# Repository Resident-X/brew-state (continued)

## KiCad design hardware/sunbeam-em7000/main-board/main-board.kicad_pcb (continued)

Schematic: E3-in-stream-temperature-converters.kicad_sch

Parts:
C640, C645: 10n; C_0603_1608Metric; Rating X7R 50V 10% 0603; MPN CL10B103KB8NNNC; LCSC C1589
C641, C642, C646, C647: 100n; C_0603_1608Metric; Rating X7R 50V 10% 0603; MPN CL10B104KB8NNNC; LCSC C1591
J620: PT1_H; JST_XH_B4B-XH-A_1x04_P2.50mm_Vertical; Rating JST XH 2.5 mm 3 A 250 V; MPN XH-4PA; LCSC C5258885
J622: PT1_2W_P; PinHeader_1x02_P2.54mm_Vertical; Rating 2.54 mm header with jumper cap; MPN 2.54-1*40P (cut) with jumper cap 2.54Sh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; LCSC C2337
J623: PT1_23W_N; PinHeader_1x02_P2.54mm_Vertical; Rating 2.54 mm header with jumper cap; MPN 2.54-1*40P (cut) with jumper cap 2.54Sh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; LCSC C2337
J625: PT2_H; JST_XH_B4B-XH-A_1x04_P2.50mm_Vertical; Rating JST XH 2.5 mm 3 A 250 V; MPN XH-4PA; LCSC C5258885
J627: PT2_2W_P; PinHeader_1x02_P2.54mm_Vertical; Rating 2.54 mm header with jumper cap; MPN 2.54-1*40P (cut) with jumper cap 2.54Sh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; LCSC C2337
J628: PT2_23W_N; PinHeader_1x02_P2.54mm_Vertical; Rating 2.54 mm header with jumper cap; MPN 2.54-1*40P (cut) with jumper cap 2.54Sh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; LCSC C2337
R640, R645: 4.02k; R_0603_1608Metric; Rating 0.1% 25ppm 0603 100mW thin film; MPN ERA3AEB4021V; LCSC C491130
R641, R646: 100k; R_0603_1608Metric; Rating 1% 100mW 75V 0603; MPN 0603WAF1003T5E; LCSC C25803
R642, R643, R647, R648: 0; R_0603_1608Metric; Rating 0603 0 ohm link; MPN 0603WAF0000T5E; LCSC C21189
R690, R691: 0; R_0603_1608Metric; Rating 0603 zero-ohm link; MPN 0603WAF0000T5E; LCSC C21189
TP620: TP_PT1_BIAS; TestPoint_Pad_D1.5mm; LCSC none
TP621: TP_PT1_RTDINP; TestPoint_Pad_D1.5mm; LCSC none
TP622: TP_PT2_BIAS; TestPoint_Pad_D1.5mm; LCSC none
TP623: TP_PT2_RTDINP; TestPoint_Pad_D1.5mm; LCSC none
TP690: TP_PT1_FORCEN_SRC; TestPoint_Pad_D1.5mm; LCSC none
TP691: TP_PT2_FORCEN_SRC; TestPoint_Pad_D1.5mm; LCSC none
U620, U621: MAX31865ATP+; TQFN-20-1EP_5x5mm_P0.65mm_EP3.1x3.1mm; Rating 4 V absolute maximum VDD and DVDD, VDD/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; MPN MAX31865ATP+T; LCSC C118474

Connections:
/In-stream temperature converters/PT1_BIAS: R640.1, TP620.1 (1_1), U620.1 (BIAS), U620.2 (REFIN+)
/In-stream temperature converters/PT1_FORCE2: R642.1, R643.1, U620.6 (FORCE2)
/In-stream temperature converters/PT1_FORCEN: J620.4, J623.2, R690.2
/In-stream temperature converters/PT1_FORCEN_SRC: R690.1, TP690.1 (1_1), U620.9 (FORCE-)
/In-stream temperature converters/PT1_FORCEP: J620.1, J622.1, R640.2, R643.2, U620.3 (REFIN-), U620.4 (ISENSOR), U620.5 (FORCE+)
/In-stream temperature converters/PT1_RTDINN: C640.2, J620.3, J623.1, U620.8 (RTDIN-)
/In-stream temperature converters/PT1_RTDINP: C640.1, J620.2, J622.2, TP621.1 (1_1), U620.7 (RTDIN+)
/In-stream temperature converters/PT2_BIAS: R645.1, TP622.1 (1_1), U621.1 (BIAS), U621.2 (REFIN+)
/In-stream temperature converters/PT2_FORCE2: R647.1, R648.1, U621.6 (FORCE2)
/In-stream temperature converters/PT2_FORCEN: J625.4, J628.2, R691.2
/In-stream temperature converters/PT2_FORCEN_SRC: R691.1, TP691.1 (1_1), U621.9 (FORCE-)
/In-stream temperature converters/PT2_FORCEP: J625.1, J627.1, R645.2, R648.2, U621.3 (REFIN-), U621.4 (ISENSOR), U621.5 (FORCE+)
/In-stream temperature converters/PT2_RTDINN: C645.2, J625.3, J628.1, U621.8 (RTDIN-)
/In-stream temperature converters/PT2_RTDINP: C645.1, J625.2, J627.2, TP623.1 (1_1), U621.7 (RTDIN+)
/PT1_CS: R641.2, U620.13 (~CS); also elsewhere on the board
/PT2_CS: R646.2, U621.13 (~CS); also elsewhere on the board
/SPI2_MISO: U620.14 (SDO), U621.14 (SDO); also elsewhere on the board
/SPI2_MOSI: U620.11 (SDI), U621.11 (SDI); also elsewhere on the board
/SPI2_SCK: U620.12 (SCLK), U621.12 (SCLK); also elsewhere on the board
GND: C641.2, C642.2, C646.2, C647.2, R642.2, R647.2, U620.10 (GND), U620.15 (DGND), U620.16 (GND), U620.21 (GND), U621.10 (GND), U621.15 (DGND), U621.16 (GND), U621.21 (GND); also elsewhere on the board

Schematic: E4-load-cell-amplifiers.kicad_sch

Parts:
C670, C672, C673, C675, C677, C678: 100n; C_0603_1608Metric; Rating X7R 50V 10% 0603; MPN CL10B104KB8NNNC; LCSC C1591
C671, C676: 10u; C_0805_2012Metric; Rating X5R 25V 10% 0805; MPN CL21A106KAYNNNE; LCSC C15850
J630: WT1_H; JST_PH_B5B-PH-K_1x05_P2.00mm_Vertical; Rating JST PH 2.0 mm 2 A 250 V; MPN KH-PH-5P-Z; LCSC C2898948
J635: WT2_H; JST_PH_B5B-PH-K_1x05_P2.00mm_Vertical; Rating JST PH 2.0 mm 2 A 250 V; MPN KH-PH-5P-Z; LCSC C2898948
R670, R671, R675, R676: 100; R_0603_1608Metric; Rating 1% 0603 100mW; MPN 0603WAF1000T5E; LCSC C22775
R672, R677: 100k; R_0603_1608Metric; Rating 1% 100mW 75V 0603; MPN 0603WAF1003T5E; LCSC C25803
TP670: TP_WT1_DATA; TestPoint_Pad_D1.0mm_Tight; LCSC none
TP671: TP_WT1_INA_P; TestPoint_Pad_D1.0mm_Tight; LCSC none
TP673: TP_WT2_INA_P; TestPoint_Pad_D1.0mm_Tight; LCSC none
U630, U631: HX711; SOIC-16_3.9x9.9mm_P1.27mm; Rating AVDD 2.6-5.5 V, DVDD 2.6-5.5 V, 24-bit,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; MPN HX711; LCSC C6705483

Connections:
/Load-cell amplifiers/WT1_INA_N: C670.2, R671.2, U630.7 (INA-)
/Load-cell amplifiers/WT1_INA_P: C670.1, R670.2, TP671.1 (1_1), U630.8 (INA+)
/Load-cell amplifiers/WT1_SN_RAW: J630.3, R671.1
/Load-cell amplifiers/WT1_SP_RAW: J630.4, R670.1
/Load-cell amplifiers/WT1_VBG: C672.1, U630.6 (VBG)
/Load-cell amplifiers/WT2_INA_N: C675.2, R676.2, U631.7 (INA-)
/Load-cell amplifiers/WT2_INA_P: C675.1, R675.2, TP673.1 (1_1), U631.8 (INA+)
/Load-cell amplifiers/WT2_SN_RAW: J635.3, R676.1
/Load-cell amplifiers/WT2_SP_RAW: J635.4, R675.1
/Load-cell amplifiers/WT2_VBG: C677.1, U631.6 (VBG)
/WT1_CLK: R672.1, U630.11 (PD_SCK); also elsewhere on the board
/WT1_DATA: TP670.1 (1_1), U630.12 (DOUT); also elsewhere on the board
/WT2_CLK: R677.1, U631.11 (PD_SCK); also elsewhere on the board
/WT2_DATA: U631.12 (DOUT); also elsewhere on the board
GND: C671.2, C672.2, C673.2, C676.2, C677.2, C678.2, J630.2, J630.5, J635.2, J635.5, R672.2, R677.2, U630.4 (VFB), U630.5 (AGND), U630.9 (INB-), U630.10 (INB+), U630.14 (XI), U630.15 (RATE), U631.4 (VFB), U631.5 (AGND), U631.9 (INB-), U631.10 (INB+), U631.14 (XI), U631.15 (RATE); also elsewhere on the board

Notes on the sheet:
Channel B, on-chip oscillator and 10 SPS rate unused

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
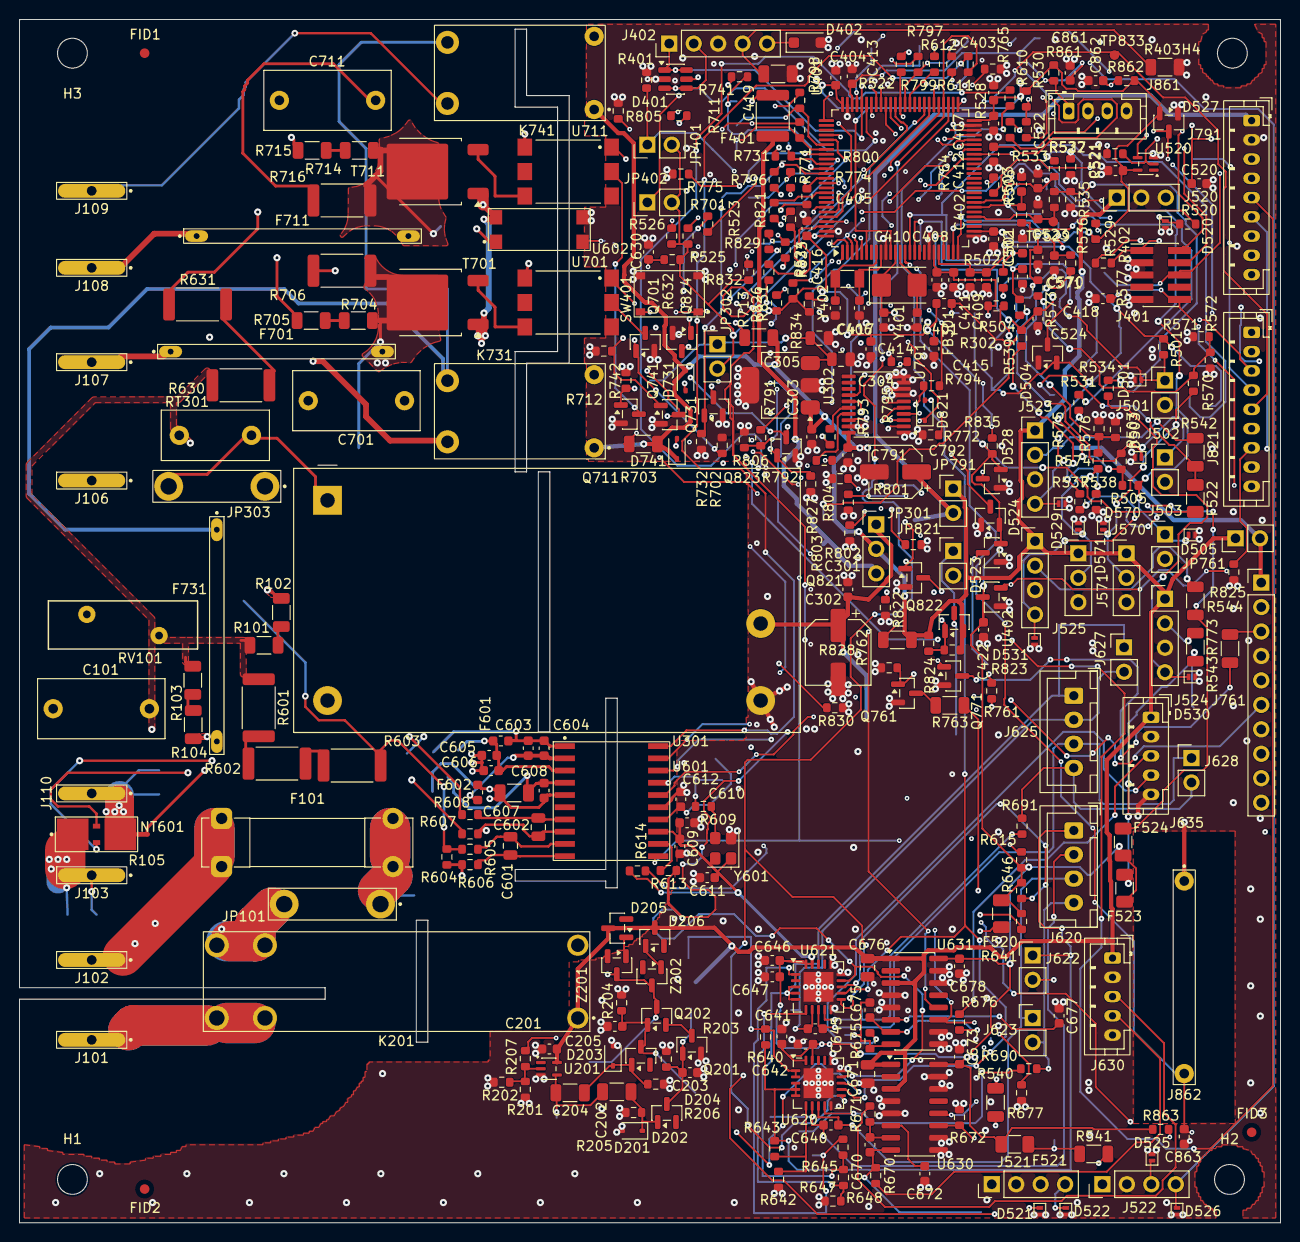
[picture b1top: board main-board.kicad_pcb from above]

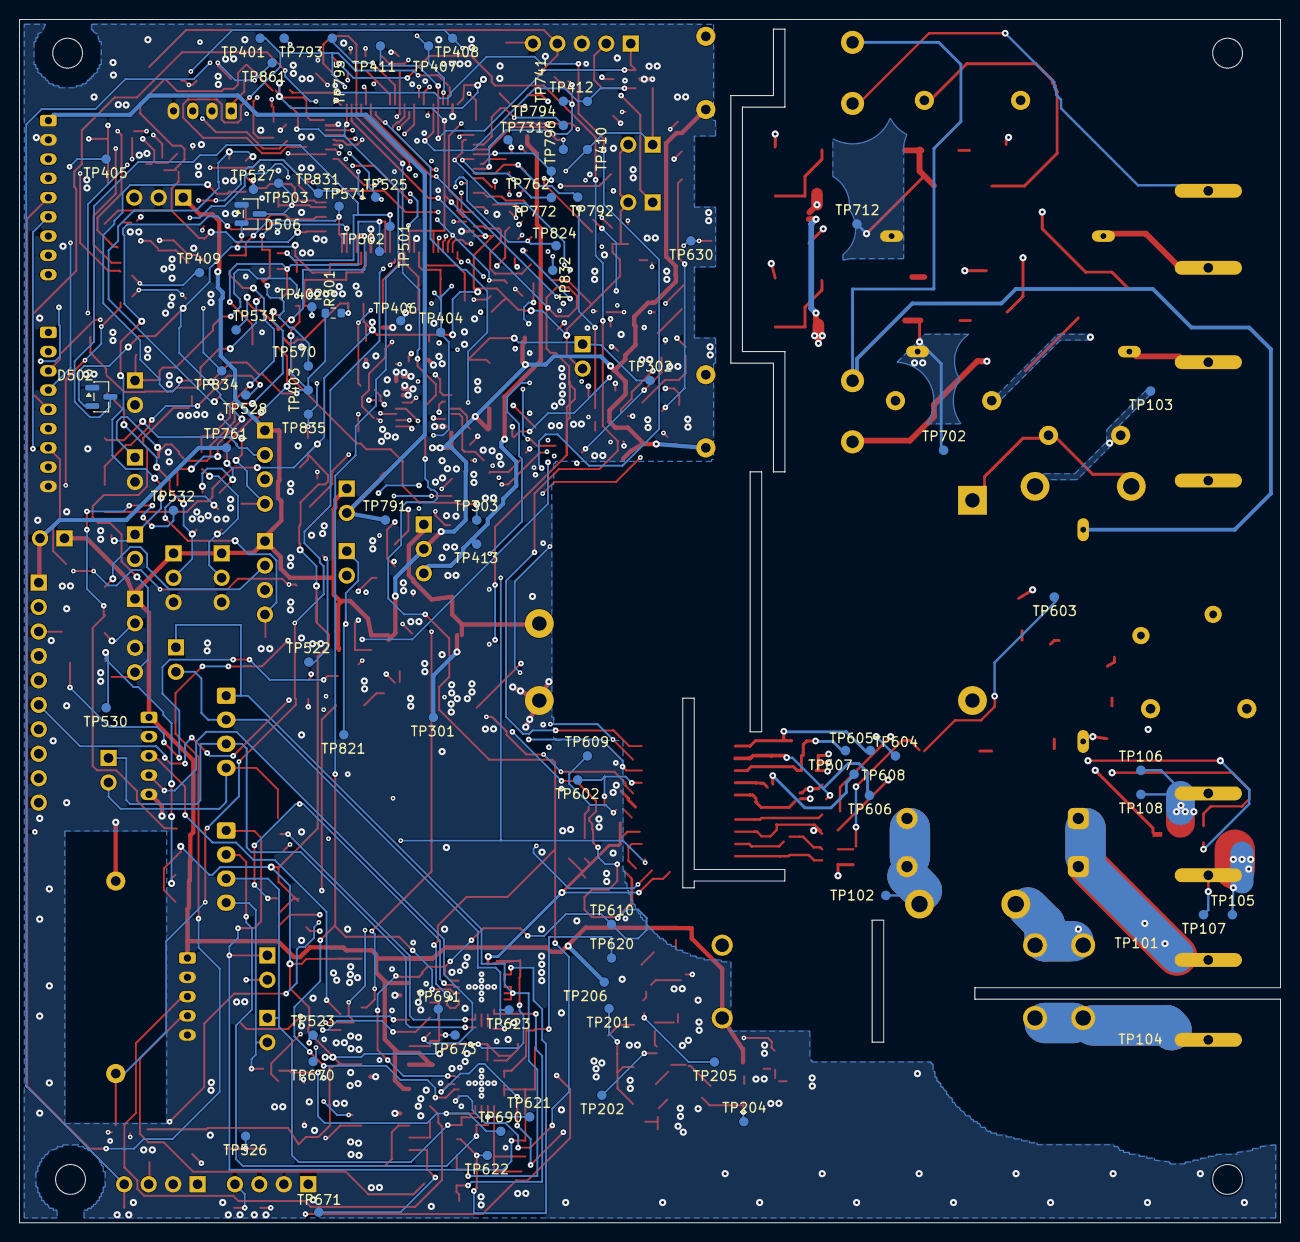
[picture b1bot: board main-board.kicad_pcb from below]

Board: 6 copper layers, 131.0 x 125.0 mm, 444 parts (85 on the bottom side), 230 nets.

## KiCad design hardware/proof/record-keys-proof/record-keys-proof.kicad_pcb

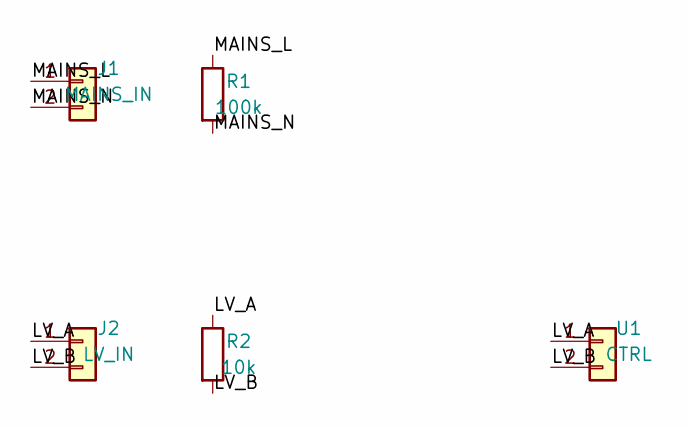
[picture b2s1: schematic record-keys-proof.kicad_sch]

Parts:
J1: MAINS_IN; PinHeader_1x02_P2.54mm_Vertical; LCSC C9000001
J2: LV_IN; PinHeader_1x02_P2.54mm_Vertical; LCSC C9000003
R1: 100k; R_Axial_DIN0207_L6.3mm_D2.5mm_P10.16mm_Horizontal; Rating 0.25W; LCSC C9000002
R2: 10k; R_Axial_DIN0207_L6.3mm_D2.5mm_P10.16mm_Horizontal; Rating 0.25W; LCSC C9000004
U1: CTRL; Controller_1x02; LCSC C9000005

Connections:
/LV_A: J2.1, R2.1, U1.1 (PA0)
/LV_B: J2.2, R2.2, U1.2 (PA1)
/MAINS_L: J1.1, R1.1
/MAINS_N: J1.2, R1.2

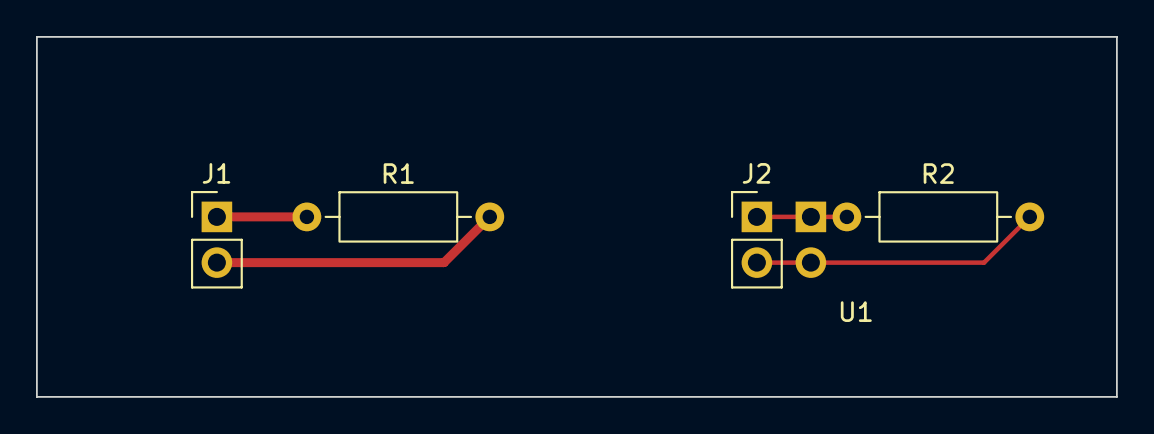
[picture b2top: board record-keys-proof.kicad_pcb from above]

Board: 2 copper layers, 60.0 x 20.0 mm, 5 parts (0 on the bottom side), 4 nets.

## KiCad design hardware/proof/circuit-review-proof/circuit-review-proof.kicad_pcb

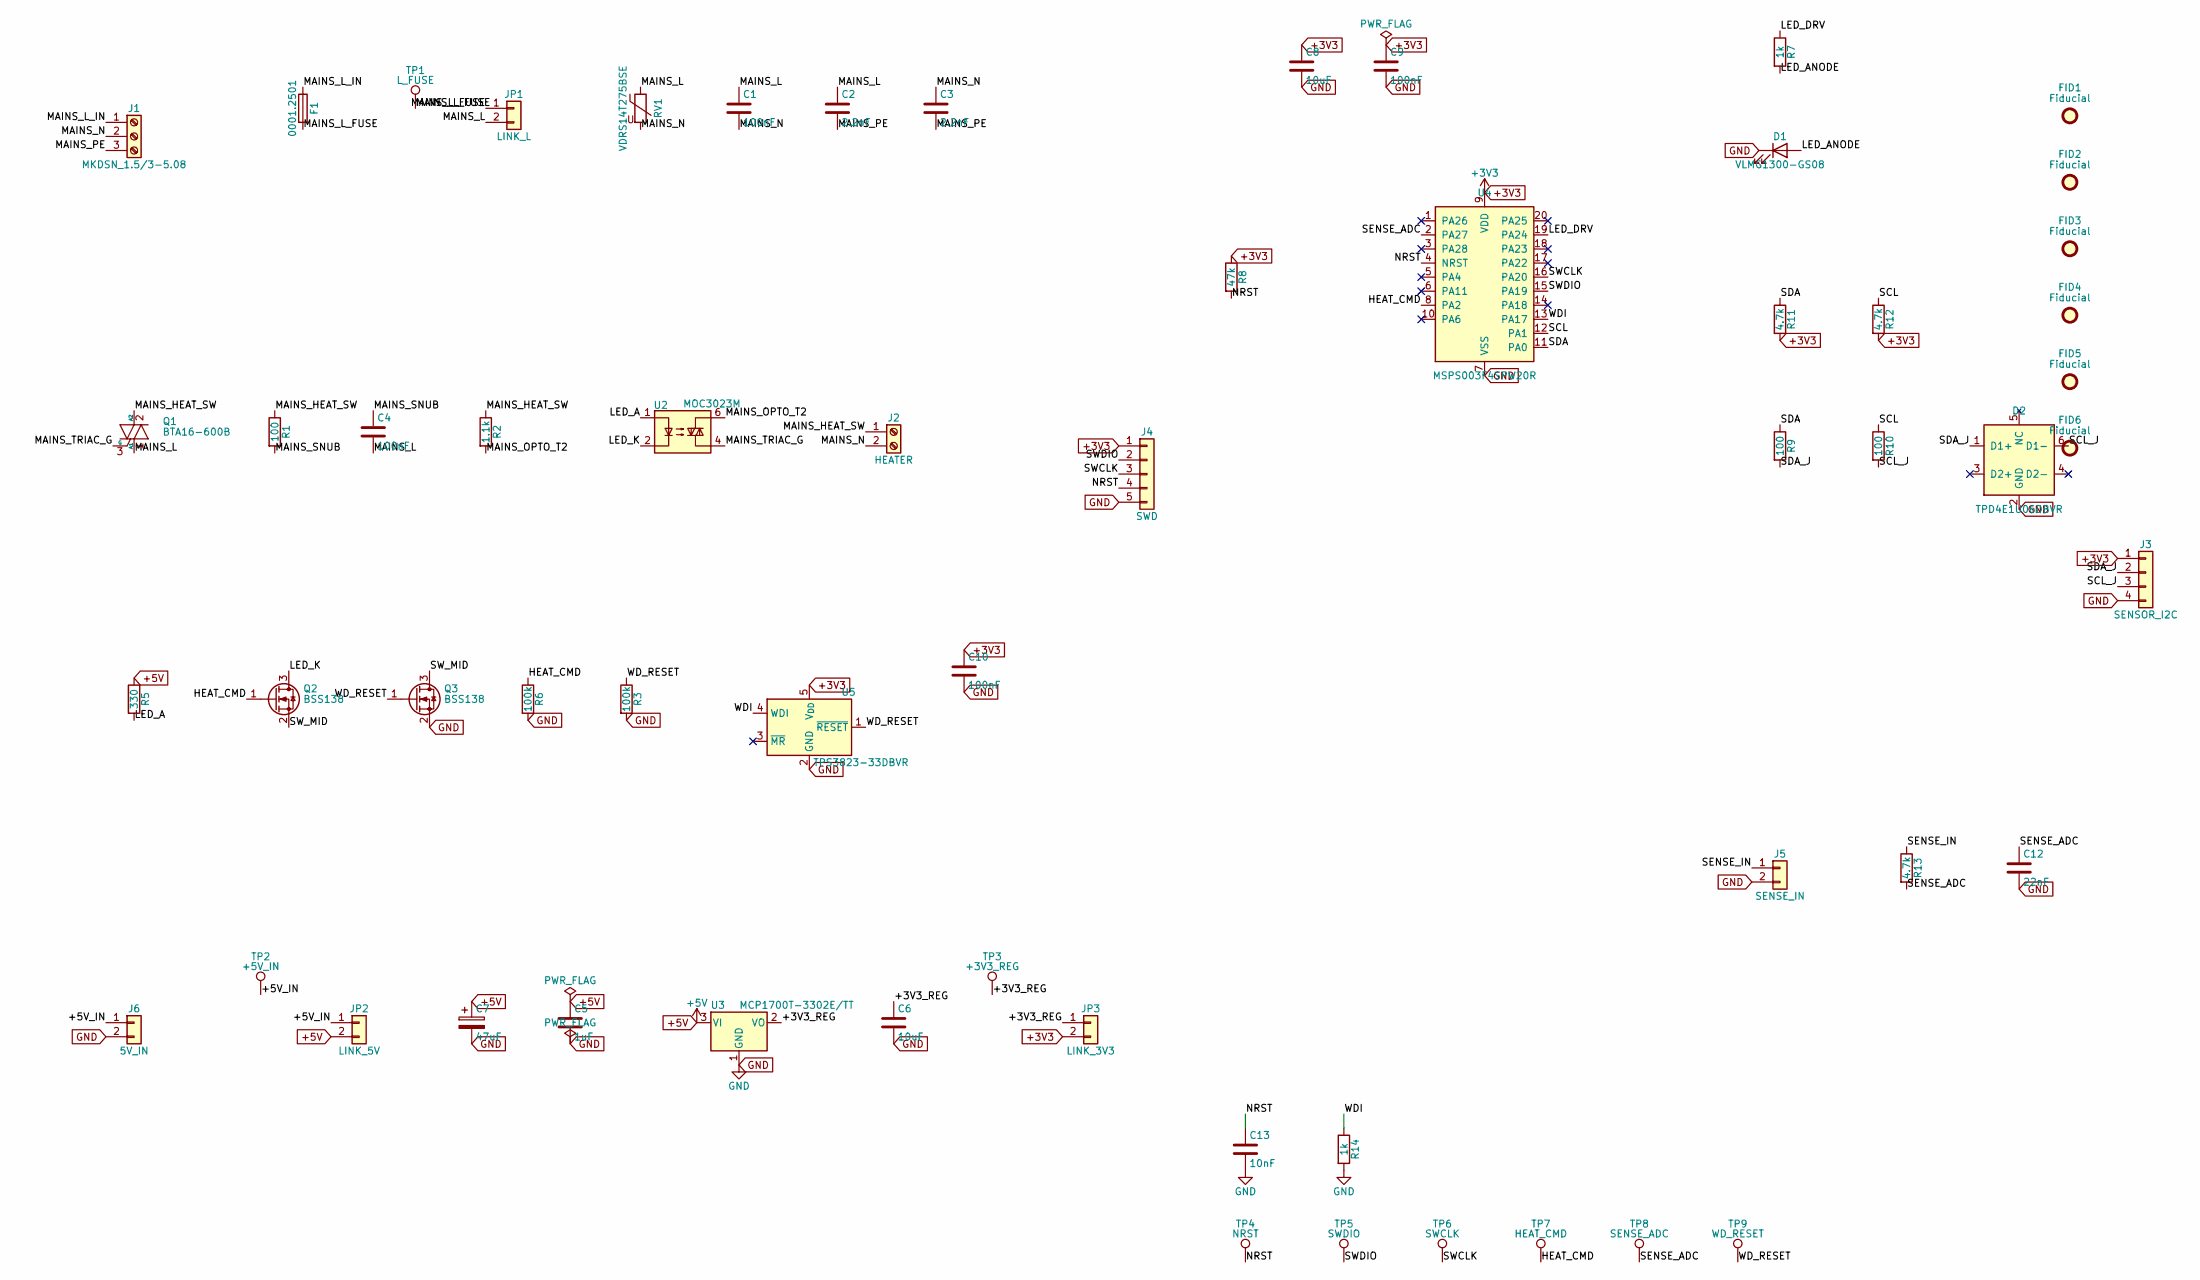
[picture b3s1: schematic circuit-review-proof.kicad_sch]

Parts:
C1, C4: 100nF; C_Rect_L18.0mm_W7.0mm_P15.00mm_FKS3_FKP3; Rating 275VAC; LCSC C9200007
C2, C3: 2.2nF; C_Disc_D7.0mm_W2.5mm_P5.00mm; Rating 250VAC; LCSC C9200008
C5: 1uF; C_0603_1608Metric; Rating 16V; LCSC C9200029
C6, C8: 10uF; C_0805_2012Metric; Rating 10V; LCSC C9200031
C7: 47uF; CP_EIA-3528-21_Kemet-B; Rating 10V; LCSC C9200028
C9, C10: 100nF; C_0603_1608Metric; Rating 16V; LCSC C9200021
C12: 22nF; C_0603_1608Metric; Rating 16V; LCSC C9200037
C13: 10nF; C_0603_1608Metric; Rating 16V; LCSC C9200036
D1: VLMG1300-GS08; LED_0603_1608Metric; Rating 30mA; LCSC C9200034
D2: TPD4E1U06DBVR; SOT-23-6; Rating 5.5V; LCSC C9200035
F1: 0001.2501; Fuseholder_Cylinder-5x20mm_Bulgin_FX0457_Horizontal_Closed; Rating 500mA 250VAC; LCSC C9200003
FID1, FID2, FID3, FID4, FID5, FID6: Fiducial; Fiducial_1mm_Mask2mm; LCSC C9200038
J1: MKDSN_1.5/3-5.08; TerminalBlock_Phoenix_MKDS-1,5-3-5.08_1x03_P5.08mm_Horizont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; Rating 320VAC 8A; LCSC C9200001
J2: HEATER; TerminalBlock_Phoenix_MKDS-1,5-2-5.08_1x02_P5.08mm_Horizont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; Rating 320VAC 8A; LCSC C9200002
J3: SENSOR_I2C; JST_XH_B4B-XH-A_1x04_P2.50mm_Vertical; Rating 3A 250V; LCSC C9200025
J4: SWD; PinHeader_1x05_P2.54mm_Vertical; Rating 3A; LCSC C9200033
J5: SENSE_IN; JST_XH_B2B-XH-A_1x02_P2.50mm_Vertical; Rating 3A 250V; LCSC C9200024
J6: 5V_IN; JST_XH_B2B-XH-A_1x02_P2.50mm_Vertical; Rating 3A 250V; LCSC C9200023
JP1: LINK_L; SolderWire-1sqmm_1x02_P7.8mm_D1.4mm_OD3.9mm; Rating 300VAC 6A; LCSC C9200005
JP2: LINK_5V; PinHeader_1x02_P2.54mm_Vertical; Rating 3A; LCSC C9200026
JP3: LINK_3V3; PinHeader_1x02_P2.54mm_Vertical; Rating 3A; LCSC C9200027
Q1: BTA16-600B; TO-220-3_Vertical; Rating 600V 16A; LCSC C9200009
Q2, Q3: BSS138; SOT-23; Rating 50V 0.22A; LCSC C9200014
R1: 100; R_2512_6332Metric; Rating 1W; LCSC C9200010
R2: 1.1k; R_1206_3216Metric; Rating 0.25W; LCSC C9200011
R3, R6: 100k; R_0603_1608Metric; Rating 0.1W; LCSC C9200015
R5: 330; R_1206_3216Metric; Rating 0.25W; LCSC C9200013
R7, R14: 1k; R_0603_1608Metric; Rating 0.1W; LCSC C9200017
R8: 47k; R_0603_1608Metric; Rating 0.1W; LCSC C9200016
R9, R10: 100; R_0603_1608Metric; Rating 0.1W; LCSC C9200018
R11, R12, R13: 4.7k; R_0603_1608Metric; Rating 0.1W; LCSC C9200019
RV1: VDRS14T275BSE; RV_Disc_D15.5mm_W5.4mm_P7.5mm; Rating 275VAC; LCSC C9200006
TP1: L_FUSE; TestPoint_Pad_D1.0mm; Rating 1A; LCSC C9200004
TP2: +5V_IN; TestPoint_Pad_D1.0mm; Rating 1A; LCSC C9200004
TP3: +3V3_REG; TestPoint_Pad_D1.0mm; Rating 1A; LCSC C9200004
TP4: NRST; TestPoint_Pad_D1.0mm; Rating 1A; LCSC C9200004
TP5: SWDIO; TestPoint_Pad_D1.0mm; Rating 1A; LCSC C9200004
TP6: SWCLK; TestPoint_Pad_D1.0mm; Rating 1A; LCSC C9200004
TP7: HEAT_CMD; TestPoint_Pad_D1.0mm; Rating 1A; LCSC C9200004
TP8: SENSE_ADC; TestPoint_Pad_D1.0mm; Rating 1A; LCSC C9200004
TP9: WD_RESET; TestPoint_Pad_D1.0mm; Rating 1A; LCSC C9200004
U2: MOC3023M; DIP-6_W7.62mm; Rating 400V; LCSC C9200012
U3: MCP1700T-3302E/TT; SOT-23; Rating 6V; LCSC C9200030
U4: MSPS003F4SPW20R; TSSOP-20_4.4x6.5mm_P0.65mm; Rating 4.1V; LCSC C9200032
U5: TPS3823-33DBVR; SOT-23-5; Rating 6V; LCSC C9200020

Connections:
/+3V3_REG: C6.1, JP3.1, TP3.1, U3.2 (VO)
/+5V_IN: J6.1, JP2.1, TP2.1
/HEAT_CMD: Q2.1 (G), R6.1, TP7.1, U4.8 (PA2)
/LED_A: R5.2, U2.1
/LED_ANODE: D1.2 (A), R7.2
/LED_DRV: R7.1, U4.19 (PA24)
/LED_K: Q2.3 (D), U2.2
/MAINS_HEAT_SW: J2.1, Q1.2 (A2), R1.1, R2.1
/MAINS_L: C1.1, C2.1, C4.2, JP1.2, Q1.1 (A1), RV1.1
/MAINS_L_FUSE: F1.2, JP1.1, TP1.1
/MAINS_L_IN: F1.1, J1.1
/MAINS_N: C1.2, C3.1, J1.2, J2.2, RV1.2
/MAINS_OPTO_T2: R2.2, U2.6
/MAINS_PE: C2.2, C3.2, J1.3
/MAINS_SNUB: C4.1, R1.2
/MAINS_TRIAC_G: Q1.3 (G), U2.4
/NRST: C13.1, J4.4, R8.2, TP4.1, U4.4 (NRST)
/SCL: R10.1, R12.1, U4.12 (PA1)
/SCL_J: D2.6 (D1-), J3.3, R10.2
/SDA: R9.1, R11.1, U4.11 (PA0)
/SDA_J: D2.1 (D1+), J3.2, R9.2
/SENSE_ADC: C12.1, R13.2, TP8.1, U4.2 (PA27)
/SENSE_IN: J5.1, R13.1
/SWCLK: J4.3, TP6.1, U4.16 (PA20)
/SWDIO: J4.2, TP5.1, U4.15 (PA19)
/SW_MID: Q2.2 (S), Q3.3 (D)
/WDI: R14.1, U4.13 (PA17), U5.4 (WDI)
/WD_RESET: Q3.1 (G), R3.1, TP9.1, U5.1 (~RESET)

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
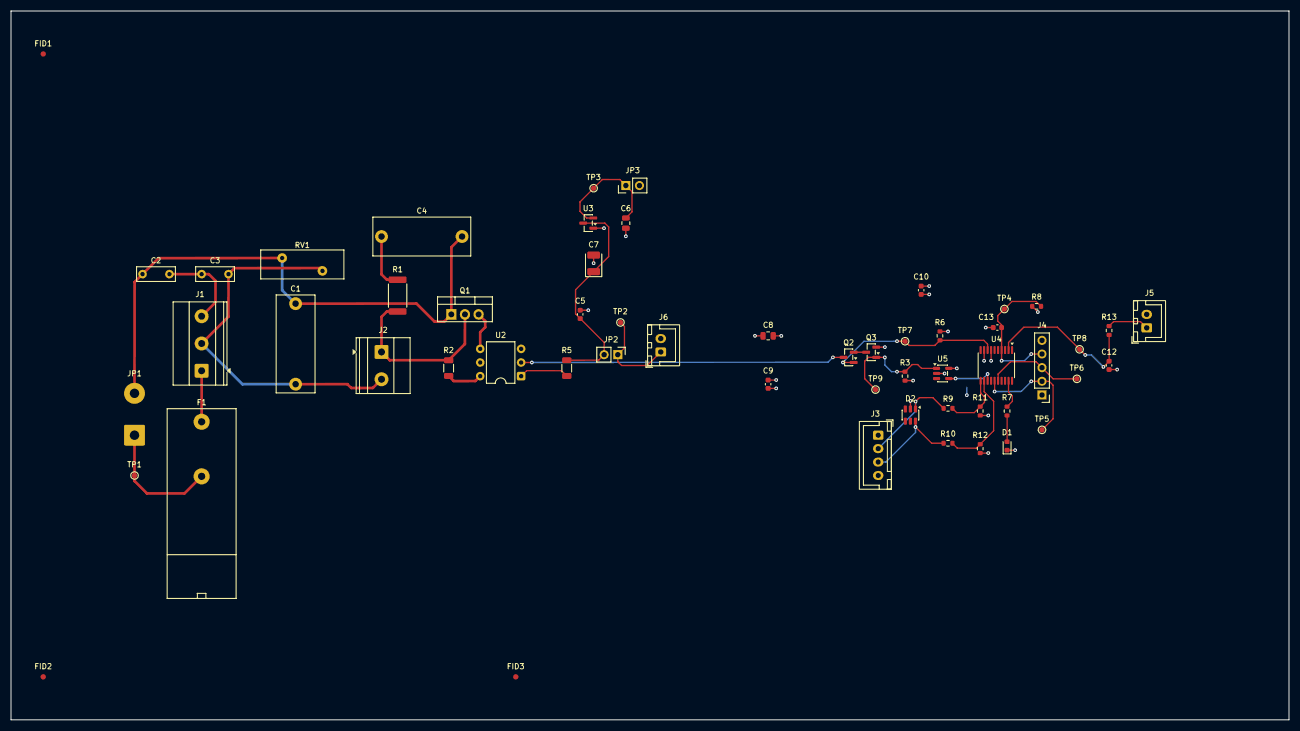
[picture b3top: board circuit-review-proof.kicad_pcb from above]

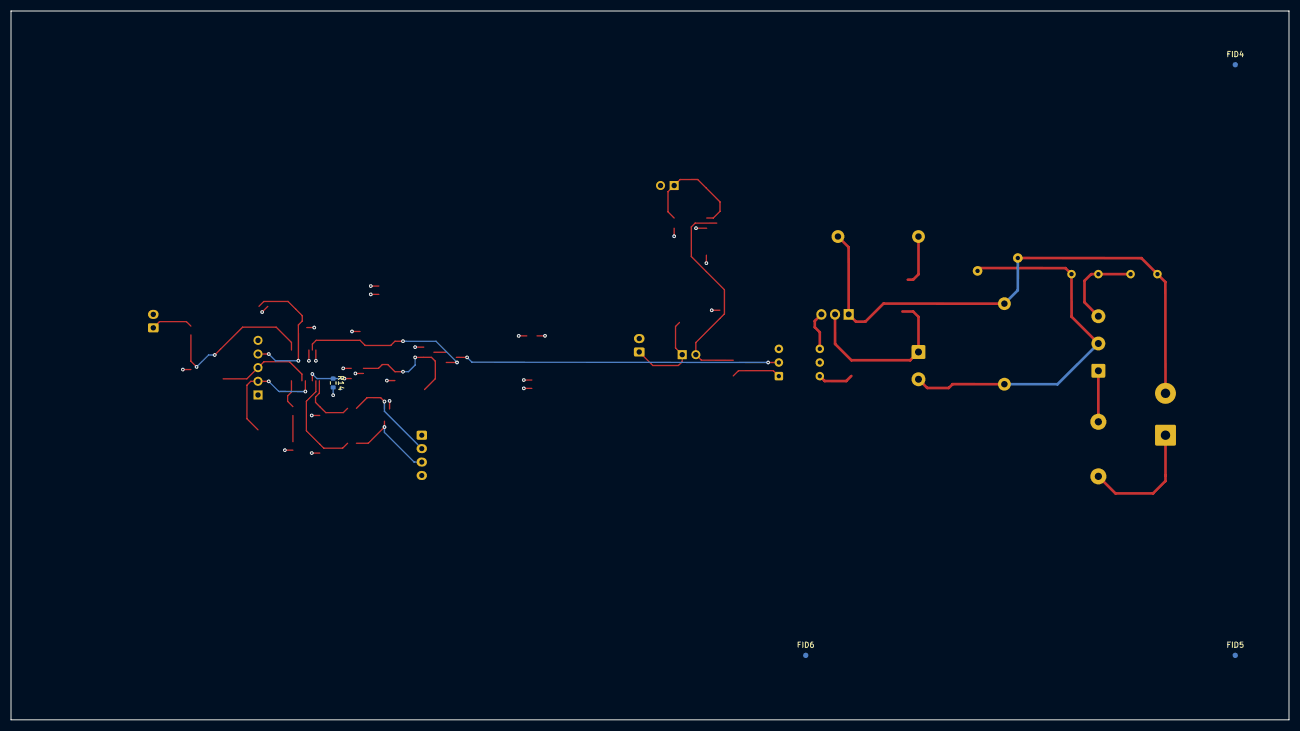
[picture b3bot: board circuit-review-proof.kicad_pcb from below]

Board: 4 copper layers, 238.0 x 132.0 mm, 60 parts (4 on the bottom side), 31 nets.

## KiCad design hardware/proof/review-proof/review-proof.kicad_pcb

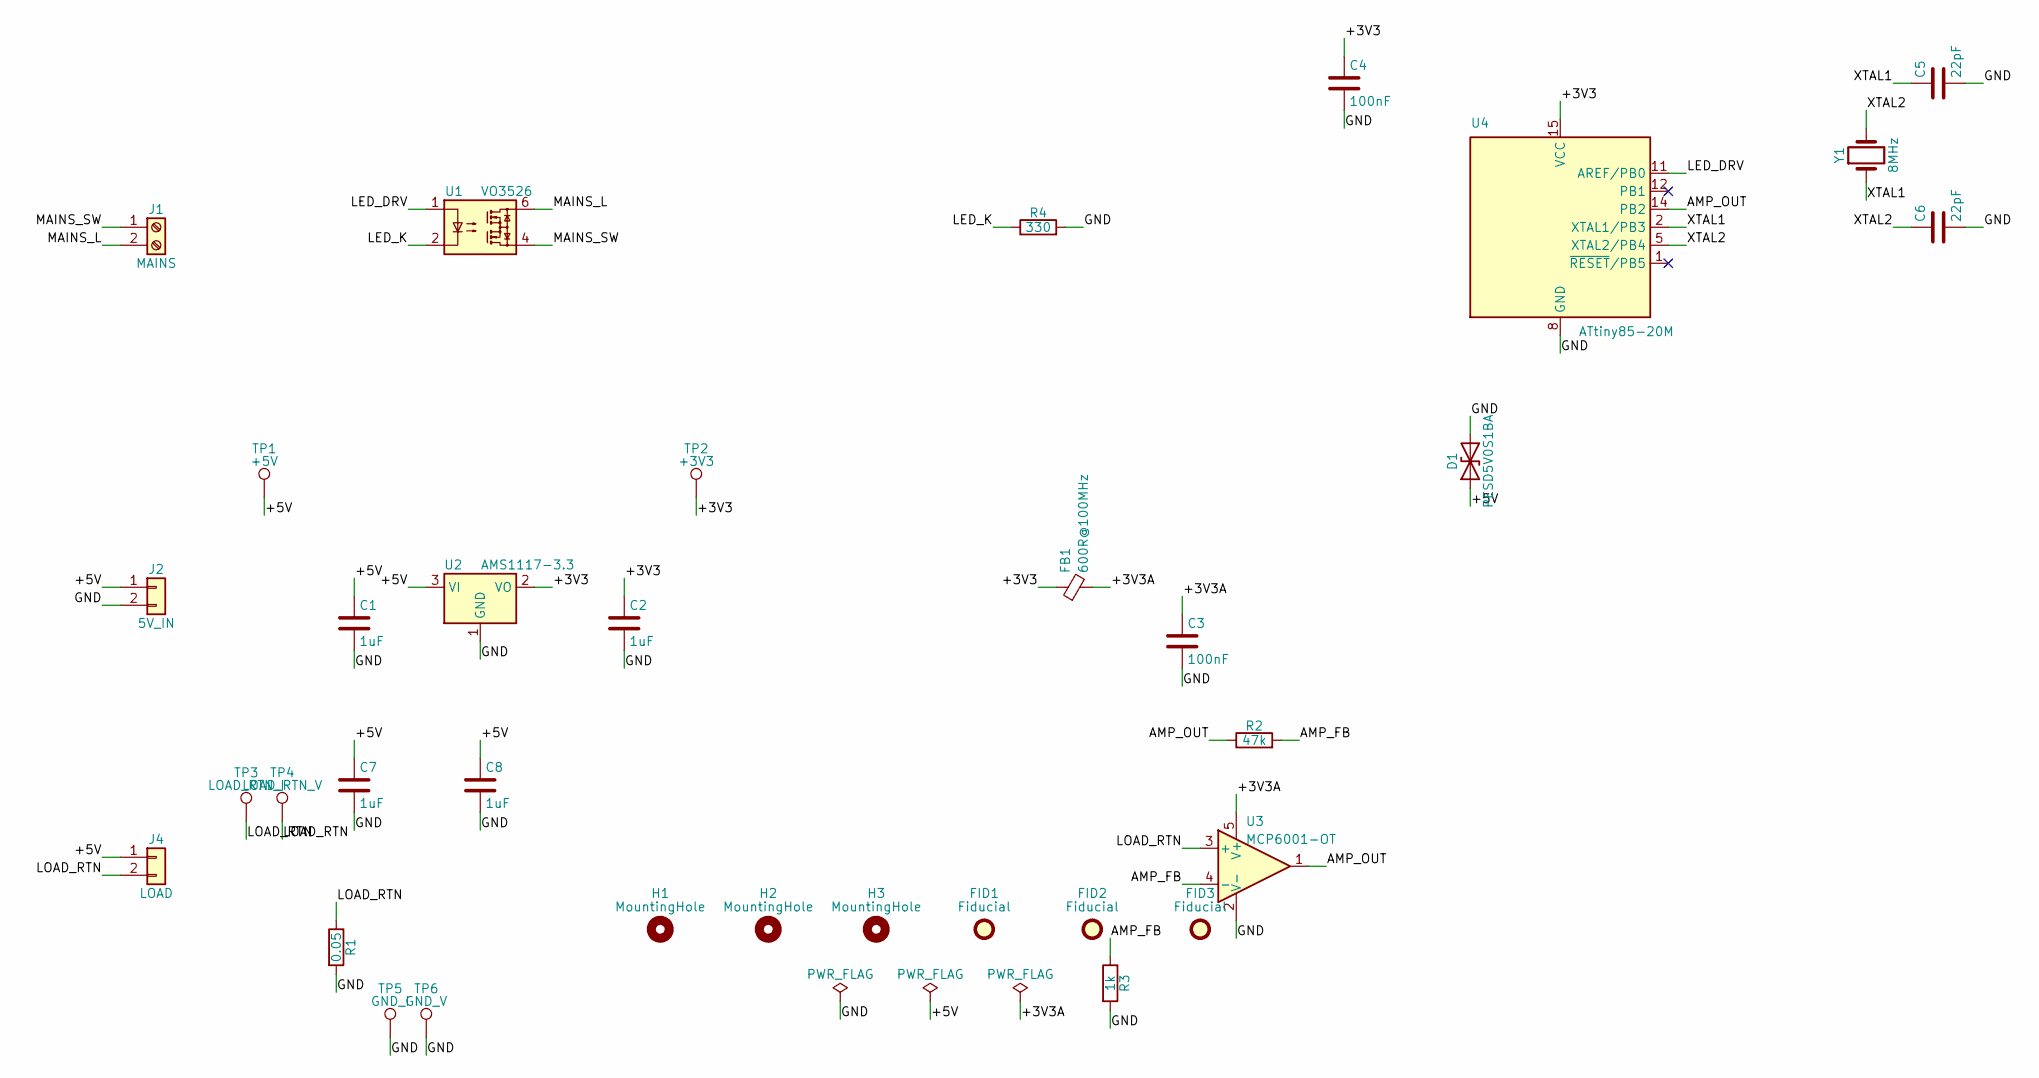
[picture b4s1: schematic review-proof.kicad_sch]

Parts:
C1: 1uF; C_0805_2012Metric; Rating 50V; LCSC C9000004
C2: 1uF; C_0805_2012Metric; Rating 50V; LCSC C9000005
C3: 100nF; C_0603_1608Metric; Rating 50V; LCSC C9000018
C4: 100nF; C_0603_1608Metric; Rating 50V; LCSC C9000020
C5: 22pF; C_0603_1608Metric; Rating 50V; LCSC C9000022
C6: 22pF; C_0603_1608Metric; Rating 50V; LCSC C9000023
C7: 1uF; C_0805_2012Metric; Rating 50V; LCSC C9000027
C8: 1uF; C_0805_2012Metric; Rating 50V; LCSC C9000028
D1: PESD5V0S1BA; D_SOD-323; LCSC C9000025
FB1: 600R@100MHz; L_0603_1608Metric; LCSC C9000017
FID1: Fiducial; Fiducial_1mm_Mask2mm; LCSC C9000032
FID2: Fiducial; Fiducial_1mm_Mask2mm; LCSC C9000033
FID3: Fiducial; Fiducial_1mm_Mask2mm; LCSC C9000034
H1: MountingHole; MountingHole_3.2mm_M3; LCSC C9000029
H2: MountingHole; MountingHole_3.2mm_M3; LCSC C9000030
H3: MountingHole; MountingHole_3.2mm_M3; LCSC C9000031
J1: MAINS; TerminalBlock_Phoenix_MKDS-1,5-2-5.08_1x02_P5.08mm_Horizont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; LCSC C9000001
J2: 5V_IN; JST_XH_B2B-XH-A_1x02_P2.50mm_Vertical; LCSC C9000003
J4: LOAD; JST_XH_B2B-XH-A_1x02_P2.50mm_Vertical; LCSC C9000006
R1: 0.05; R_2512_6332Metric; Rating 0.25W; LCSC C9000007
R2: 47k; R_0603_1608Metric; Rating 0.25W; LCSC C9000015
R3: 1k; R_0603_1608Metric; Rating 0.25W; LCSC C9000016
R4: 330; R_0603_1608Metric; Rating 0.25W; LCSC C9000024
TP1: +5V; TestPoint_Pad_D1.0mm; LCSC C9000008
TP2: +3V3; TestPoint_Pad_D1.0mm; LCSC C9000009
TP3: LOAD_RTN_I; TestPoint_Pad_D1.0mm; LCSC C9000010
TP4: LOAD_RTN_V; TestPoint_Pad_D1.0mm; LCSC C9000011
TP5: GND_I; TestPoint_Pad_D1.0mm; LCSC C9000012
TP6: GND_V; TestPoint_Pad_D1.0mm; LCSC C9000013
U1: VO3526; DIP-5-6_W7.62mm; LCSC C9000002
U2: AMS1117-3.3; SOT-223-3_TabPin2; LCSC C9000026
U3: MCP6001-OT; SOT-23-5; LCSC C9000014
U4: ATtiny85-20M; QFN-20-1EP_4x4mm_P0.5mm_EP2.6x2.6mm; LCSC C9000019
Y1: 8MHz; Crystal_SMD_5032-2Pin_5.0x3.2mm; LCSC C9000021

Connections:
/+3V3: C2.1, C4.1, FB1.1, TP2.1, U2.2 (VO), U4.15 (VCC)
/+3V3A: C3.1, FB1.2, U3.5 (V+)
/+5V: C1.1, C7.1, C8.1, D1.1 (A1), J2.1, J4.1, TP1.1, U2.3 (VI)
/AMP_FB: R2.2, R3.1, U3.4 (-)
/AMP_OUT: R2.1, U3.1, U4.14 (PB2)
/GND: C1.2, C2.2, C3.2, C4.2, C5.2, C6.2, C7.2, C8.2, D1.2 (A2), J2.2, R1.2, R3.2, R4.2, TP5.1, TP6.1, U2.1 (GND), U3.2 (V-), U4.8 (GND), U4.21 (GND)
/LED_DRV: U1.1, U4.11 (AREF/PB0)
/LED_K: R4.1, U1.2
/LOAD_RTN: J4.2, R1.1, TP3.1, TP4.1, U3.3 (+)
/MAINS_L: J1.2, U1.6
/MAINS_SW: J1.1, U1.4
/XTAL1: C5.1, U4.2 (XTAL1/PB3), Y1.1
/XTAL2: C6.1, U4.5 (XTAL2/PB4), Y1.2

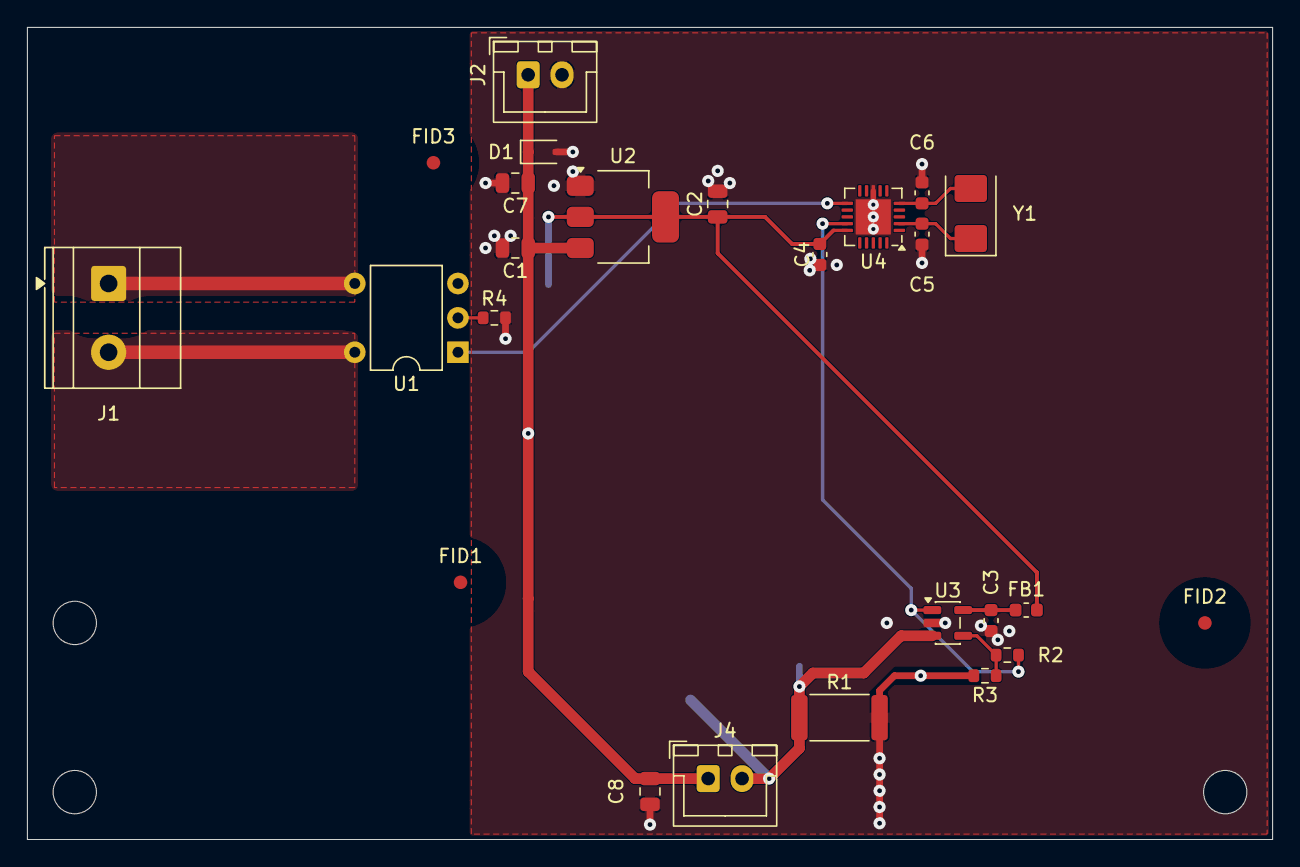
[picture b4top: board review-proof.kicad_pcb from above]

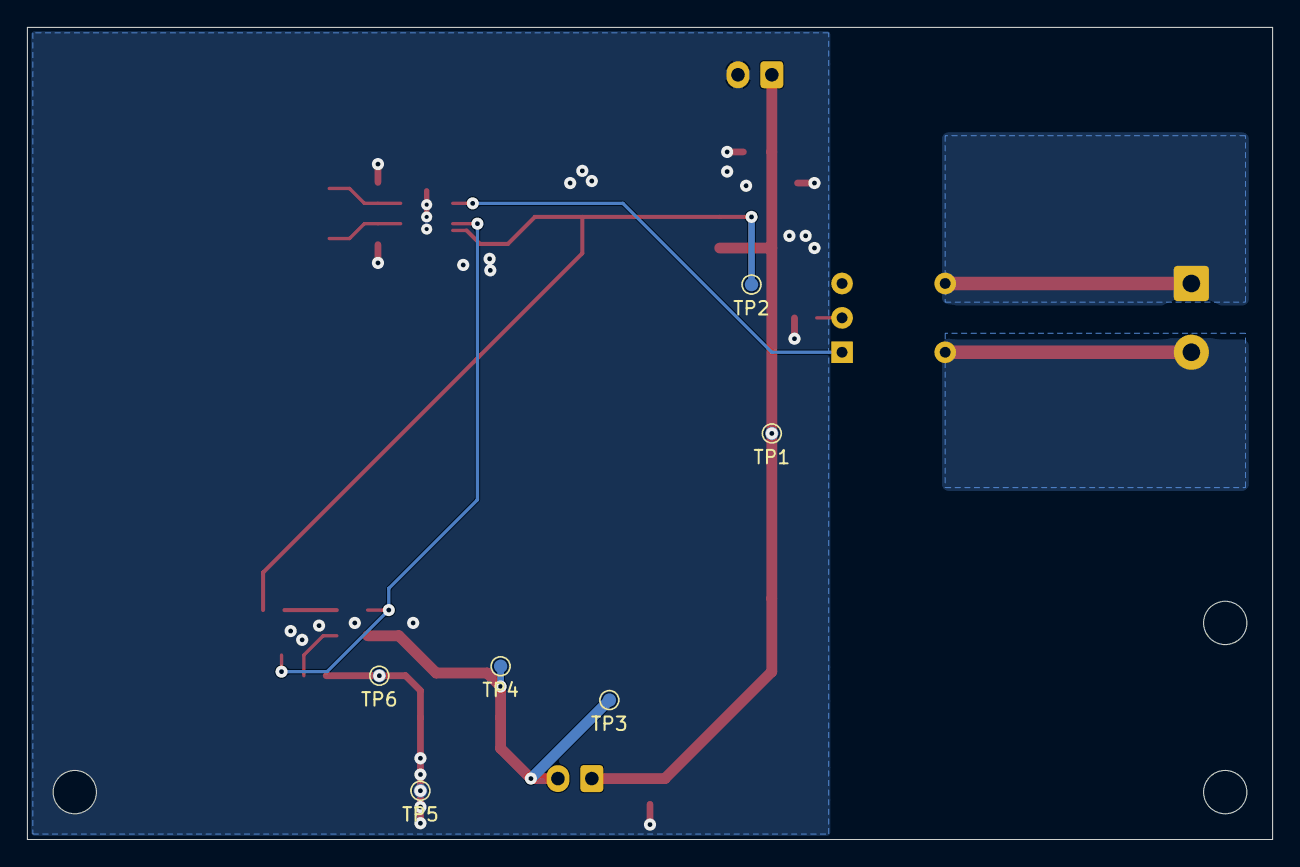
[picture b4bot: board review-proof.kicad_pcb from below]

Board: 4 copper layers, 92.0 x 60.0 mm, 34 parts (6 on the bottom side), 13 nets.
